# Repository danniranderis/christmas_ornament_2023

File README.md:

# Christmas Tree Ornament 2023
This project is the start of hopefully a yearly tradition in creating an electronics project for the Christmas holidays.  
The pcb resembles a Christmas tree with silkscreen ornaments and LEDs for effect.

There are two modes in the way the PCB can be used;

1. Mode (1) is a setup with two sets of red LEDs that flashes in a shifting pattern controlled by a 555-timer circuit.
2. Mode (2) is a simple power-configuration for slow-flashing RGB LEDs.

Please see schematics documentation for guidance in choosing which mode to solder and create.

## Hardware
The "Hardware" directory within this repository contains PCB design as KiCAD project.

## Mechanical
The "Mechanical" directory within this repository contains 3D (FDM) printable mechanical parts as FreeCAD project and `.3mf` files.

## Documentation
The "Documentation" directory within this repository contains various documentation-files for the project. Find PDFs, images and alike herewithin.

## Credits
- Danni Randeris <danni@danniranderis.dk>

Graphics from public domain kindly used.
- [Candy Cane](https://openclipart.org/detail/189393/candy-cane) by [darkness3560](https://openclipart.org/artist/darkness3560) (CC0 - Public Domain)
- [Snowflake Silhouette](https://openclipart.org/detail/292679/snowflake-silhouette) by [GDJ](https://openclipart.org/artist/GDJ) (CC0 - Public Domain)
- [SnowFlake04](https://openclipart.org/detail/268022/snowflake04) by [Doc46](https://openclipart.org/artist/Doc46) (CC0 - Public Domain)
- [Weather Symbols: Snow](https://openclipart.org/detail/22006/weather-symbols-snow) by [nicubunu](https://openclipart.org/artist/nicubunu) (CC0 - Public Domain)
- [Happy Snowman](https://openclipart.org/detail/269470/happy-snowman) by [kdog5454](https://openclipart.org/artist/kdog5454) (CC0 - Public Domain)
- [Santa Hat](https://openclipart.org/detail/323412/santa-hat) by [NicholasJudy567](https://openclipart.org/artist/NicholasJudy567) (CC0 - Public Domain)
- [Santa 3](https://openclipart.org/detail/284931/santa-3) by [Firkin](https://openclipart.org/artist/Firkin) (CC0 - Public Domain)
- [Bell vector](https://shmector.com/free-vector/other/bell_vector/14-0-882) by SHMRCTOR.COM (CC0 - Public Domain)

## License
Copyright 2023 Danni Randeris

This project is licensed under the TAPR Open Hardware License (www.tapr.org/OHL). The "license" folder within this repository contains a copy of this license in plain text format.

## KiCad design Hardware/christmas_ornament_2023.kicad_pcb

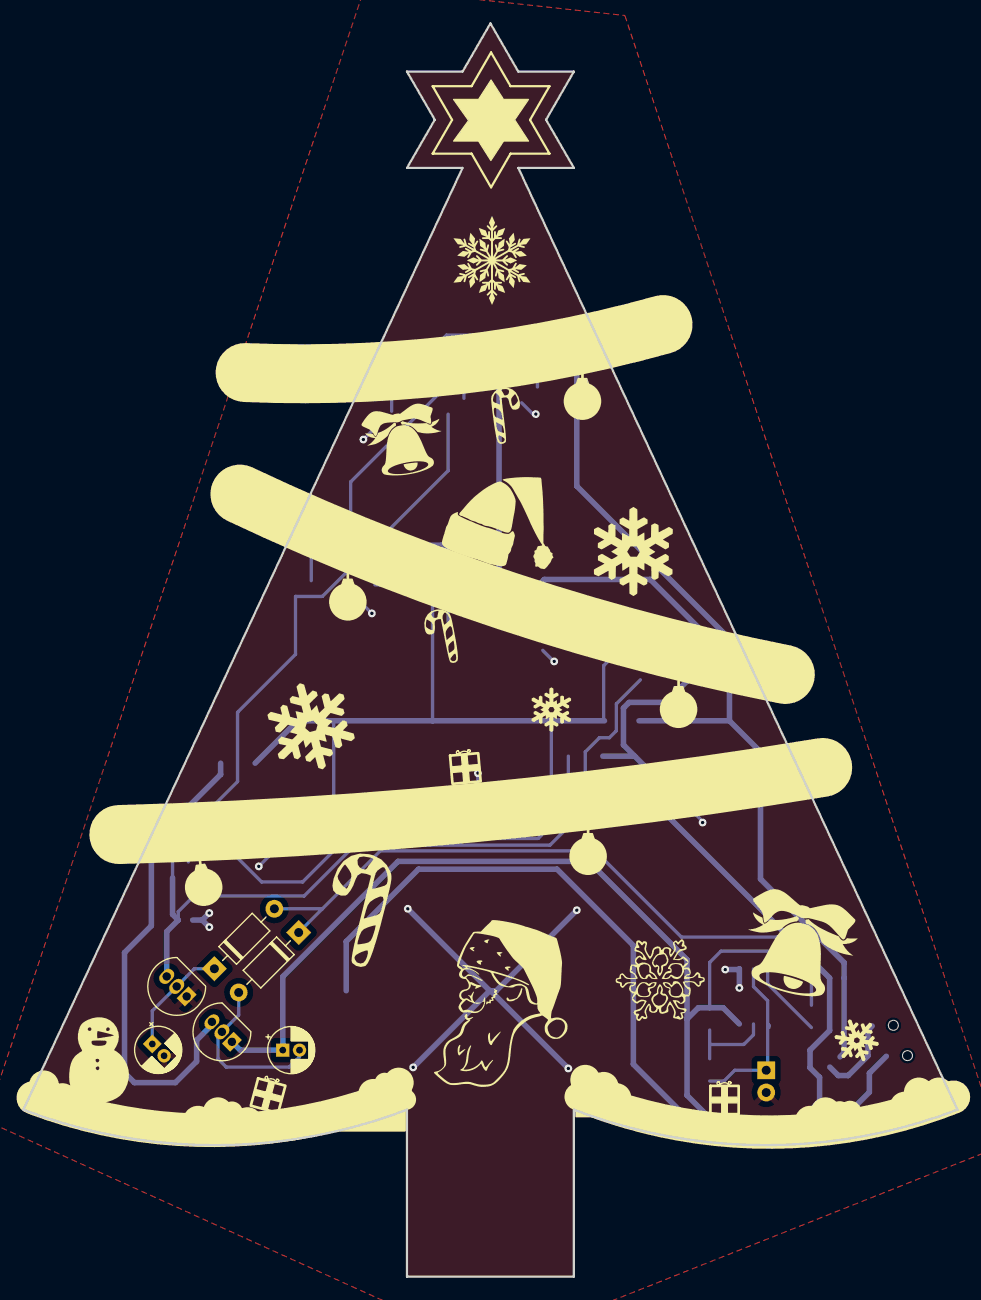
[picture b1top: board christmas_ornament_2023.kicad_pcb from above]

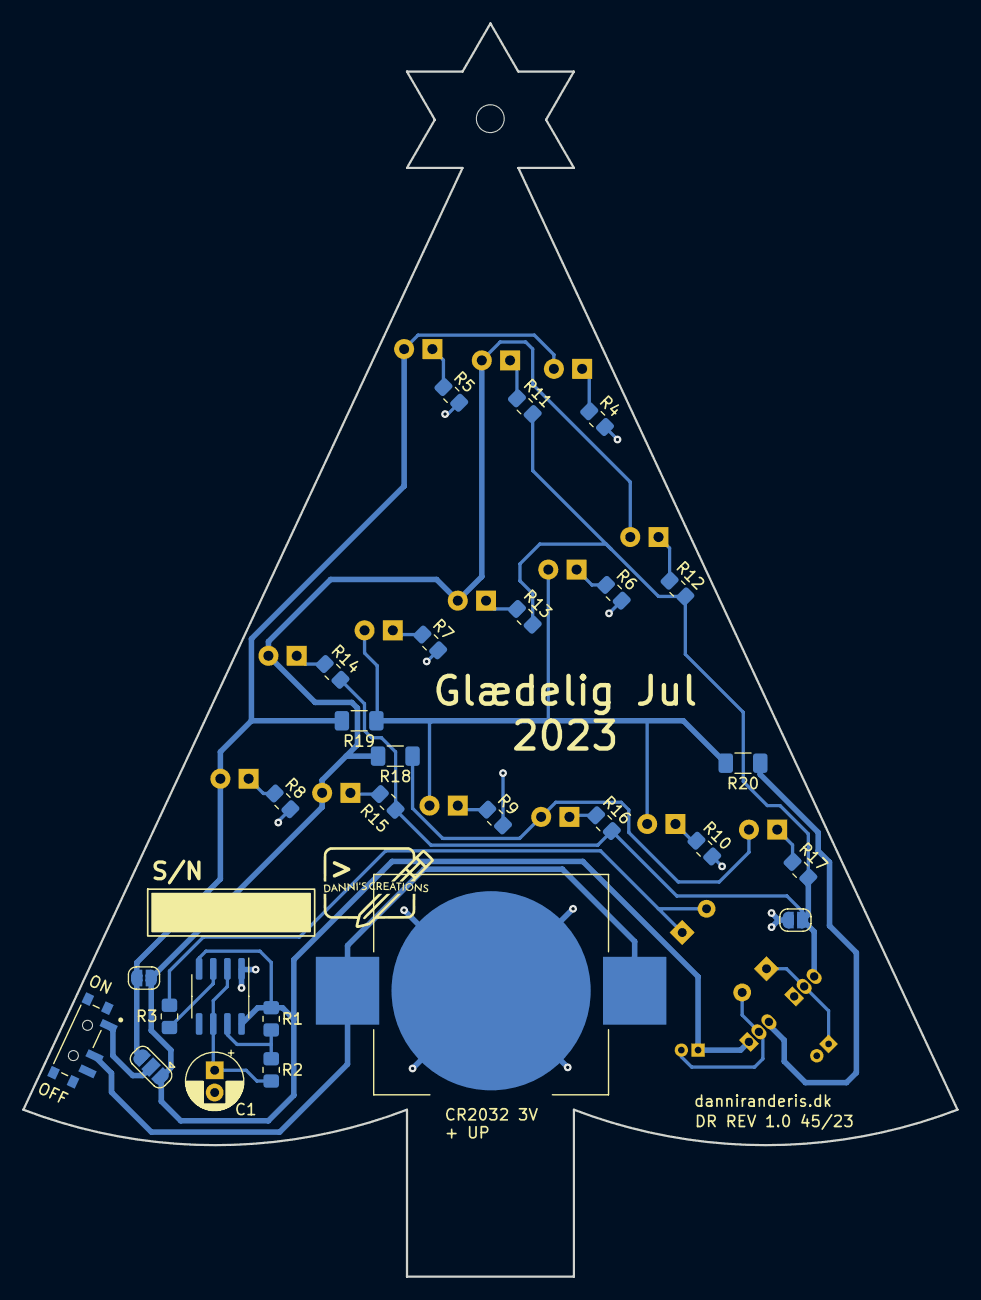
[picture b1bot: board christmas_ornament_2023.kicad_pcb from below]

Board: 2 copper layers, 83.9 x 112.6 mm, 47 parts (27 on the bottom side), 28 nets.

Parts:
BT1: CR2032 3V; BAT_BAT-HLD-003-SMT
C1: 4.7uF; CP_Radial_D5.0mm_P2.00mm
C2, C3: 10uF, 16V; CP_Radial_D4.0mm_P1.50mm
D1, D2: 1N4148; D_DO-35_SOD27_P7.62mm_Horizontal
D3, D4, D5, D6, D7, D8, D9, D10, D11, D12, D13, D14, D15, D16: LED; LED_D3.0mm
JP1: Mode select; SolderJumper-3_P1.3mm_Open_RoundedPad1.0x1.5mm
JP2, JP3: mode2; SolderJumper-2_P1.3mm_Open_RoundedPad1.0x1.5mm
Q1: 2N3906; TO-92_Inline
Q2: 2N3904; TO-92_Inline
R1: 3k; R_0805_2012Metric_Pad1.20x1.40mm_HandSolder
R2: 330k; R_0805_2012Metric_Pad1.20x1.40mm_HandSolder
R3: 2k2; R_0805_2012Metric_Pad1.20x1.40mm_HandSolder
R4, R5, R6, R7, R8, R9, R10, R11, R12, R13, R14, R15, R16, R17: 470; R_0805_2012Metric_Pad1.20x1.40mm_HandSolder
R18, R19, R20: 0; R_1206_3216Metric_Pad1.30x1.75mm_HandSolder
SW1: PCM12SMTR; SW_PCM12SMTR
U1: TLC555CDR; SOIC-8_3.9x4.9mm_P1.27mm

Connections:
GND: BT1.N, C1.2, C2.2, JP3.2 (B), Q2.1 (E), R4.2, R5.2, R6.2, R7.2, R8.2, R9.2, R10.2, U1.1 (GND)
unnamed: C3.2, D1.2 (A), Q1.2 (B)
unnamed: D1.1 (K), D2.2 (A), R3.2
unnamed: C2.1, D2.1 (K), Q2.2 (B)
unnamed: D3.2 (A), D4.2 (A), D5.2 (A), D6.2 (A), D7.2 (A), D8.2 (A), D9.2 (A), JP1.3 (B), JP2.1 (A), R19.1, R19.2, R20.2
unnamed: D3.1 (K), R4.1
unnamed: D4.1 (K), R5.1
unnamed: D5.1 (K), R6.1
unnamed: D6.1 (K), R7.1
unnamed: D7.1 (K), R8.1
unnamed: D8.1 (K), R9.1
unnamed: D9.1 (K), R10.1
unnamed: C3.1, D10.2 (A), D11.2 (A), D12.2 (A), D13.2 (A), D14.2 (A), JP1.1 (A), JP2.2 (B), Q1.1 (E), R1.1, R18.2, U1.4 (RESET), U1.8 (VCC)
unnamed: D10.1 (K), R11.1
unnamed: D11.1 (K), R12.1
unnamed: D12.1 (K), R13.1
unnamed: D13.1 (K), R14.1
unnamed: D14.1 (K), R15.1
unnamed: D15.2 (A), D16.2 (A), R18.1
unnamed: D15.1 (K), R16.1
unnamed: D16.1 (K), R17.1
unnamed: JP1.2 (C), SW1.1 (A)
unnamed: JP3.1 (A), Q2.3 (C), R11.2, R12.2, R13.2, R14.2, R15.2, R16.2, R17.2
unnamed: Q1.3 (C), R20.1
unnamed: BT1.P1, BT1.P2, SW1.2 (B)
unnamed: R1.2, R2.1, U1.7 (DISCH)
unnamed: R3.1, U1.3 (OUT)
unnamed: C1.1, R2.2, U1.2 (TRIG), U1.6 (THRES)

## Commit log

2023-09-17 Initialization of project.
2023-11-12 Revision 1.0 of Christmas Ornament 2023
2023-11-12 Generating images and documentation.

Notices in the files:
parts and their libraries:
Converted from SVG (CC0): https://openclipart.org/detail/323412/santa-hat
Converted from SVG (CC0): https://openclipart.org/detail/284931/santa-3
Converted from SVG (CC0): https://openclipart.org/detail/189393/candy-cane
Converted from SVG (CC0): https://openclipart.org/detail/269470/happy-snowman
